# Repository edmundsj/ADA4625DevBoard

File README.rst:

ADA4625 TIA Development Board
===============================
This is a development board for the ADA4625 used as a low-noise a transimpedance amplifier.

Features
----------
- Low noise (140nV/rtHz measured at output with 1MOhm resistor, 140fA/rtHz input-referred)
- M3 standoffs
- Separate SMA inputs for + and -
- Power supplied by banana jacks (V+, V-, GND)
- Optional ESD protection diodes and output load filter
- Test points galore

Issues in Version 1
--------------------
- [FIXED v2.1] Gerbers not updated from v1
- [FIXED v2] No labeling of power, input/outputs
- [FIXED v2] board was unnecessarily large
- [FIXED v2]No name / version number on board

Bill of Materials
-------------------

.. csv-table::
    :header-rows: 1
    :file: bom.csv
    :widths: 25 25 25 25 25

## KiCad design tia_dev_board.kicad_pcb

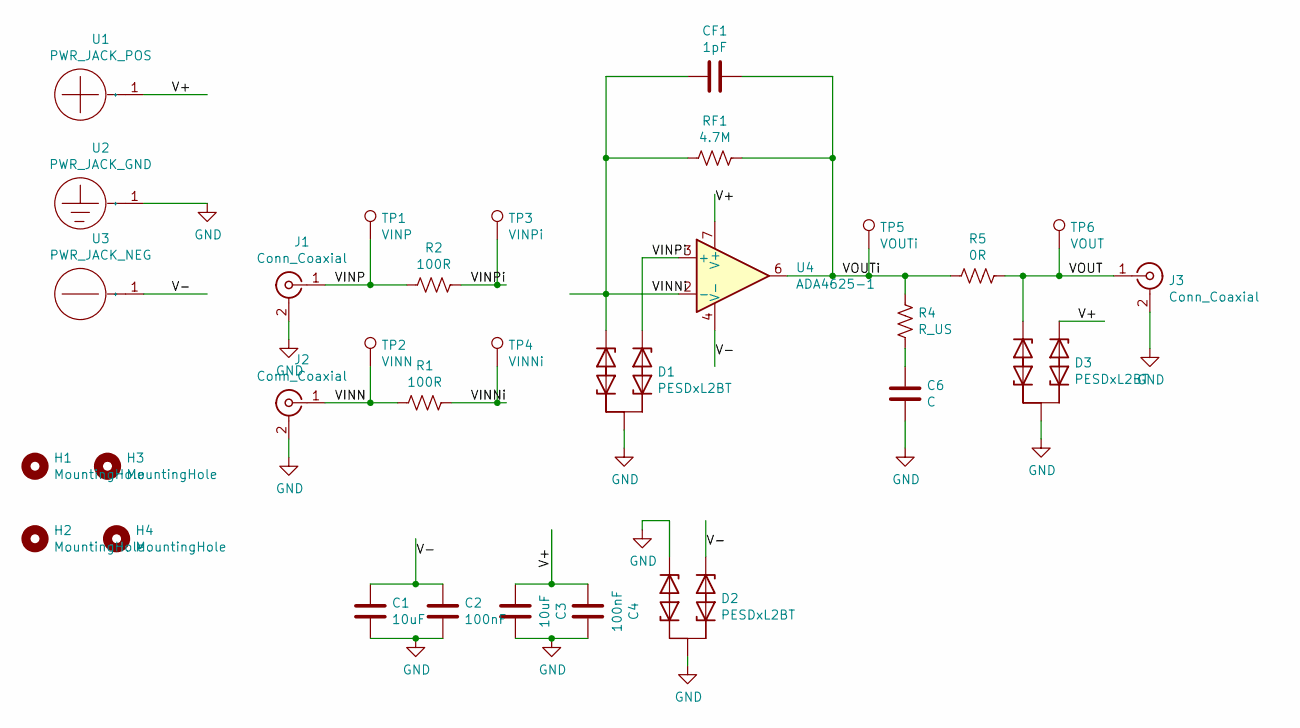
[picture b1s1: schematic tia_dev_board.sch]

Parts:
C1, C3: 10uF; C_0805_2012Metric_Pad1.15x1.40mm_HandSolder
C2, C4: 100nF; C_0805_2012Metric_Pad1.15x1.40mm_HandSolder
C6: C; C_0805_2012Metric_Pad1.15x1.40mm_HandSolder
CF1: 1pF; C_0805_2012Metric_Pad1.15x1.40mm_HandSolder
D1, D2, D3: PESDxL2BT; SC-59_Handsoldering
H1, H2, H3, H4: MountingHole; m3_mounting_hole
J1, J2, J3: Conn_Coaxial; CON-SMA-EDGE-S
R1, R2: 100R; C_0805_2012Metric_Pad1.15x1.40mm_HandSolder
R4: R_US; C_0805_2012Metric_Pad1.15x1.40mm_HandSolder
R5: 0R; C_0805_2012Metric_Pad1.15x1.40mm_HandSolder
RF1: 4.7M; C_0805_2012Metric_Pad1.15x1.40mm_HandSolder
TP1: VINP; TestPoint_Keystone_5000-5004_Miniature
TP2: VINN; TestPoint_Keystone_5000-5004_Miniature
TP3: VINPi; TestPoint_Keystone_5000-5004_Miniature
TP4: VINNi; TestPoint_Keystone_5000-5004_Miniature
TP5: VOUTi; TestPoint_Keystone_5000-5004_Miniature
TP6: VOUT; TestPoint_Keystone_5000-5004_Miniature
U1: PWR_JACK_POS; Banana_Jack_1Pin
U2: PWR_JACK_GND; Banana_Jack_1Pin
U3: PWR_JACK_NEG; Banana_Jack_1Pin
U4: ADA4625-1; SOIC-8-1EP_3.9x4.9mm_P1.27mm_EP2.29x3mm_ThermalVias

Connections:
/V+: C3.2, C4.2, D3.2 (V2), U1.1, U4.7 (V+)
/V-: C1.1, C2.1, D2.2 (V2), U3.1, U4.4 (V-)
/VINN: J2.1 (In), R1.2, TP2.1
/VINNi: CF1.2, D1.1 (V1), R1.1, RF1.2, TP4.1, U4.2 (-)
/VINP: J1.1 (In), R2.2, TP1.1
/VINPi: D1.2 (V2), R2.1, TP3.1, U4.3 (+)
/VOUT: D3.1 (V1), J3.1 (In), R5.1, TP6.1
/VOUTi: CF1.1, R4.1, R5.2, RF1.1, TP5.1, U4.6
GND: C1.2, C2.2, C3.1, C4.1, C6.2, D1.3 (GND), D2.1 (V1), D2.3 (GND), D3.3 (GND), J1.2 (Ext), J2.2 (Ext), J3.2 (Ext), U2.1
unnamed: C6.1, R4.2

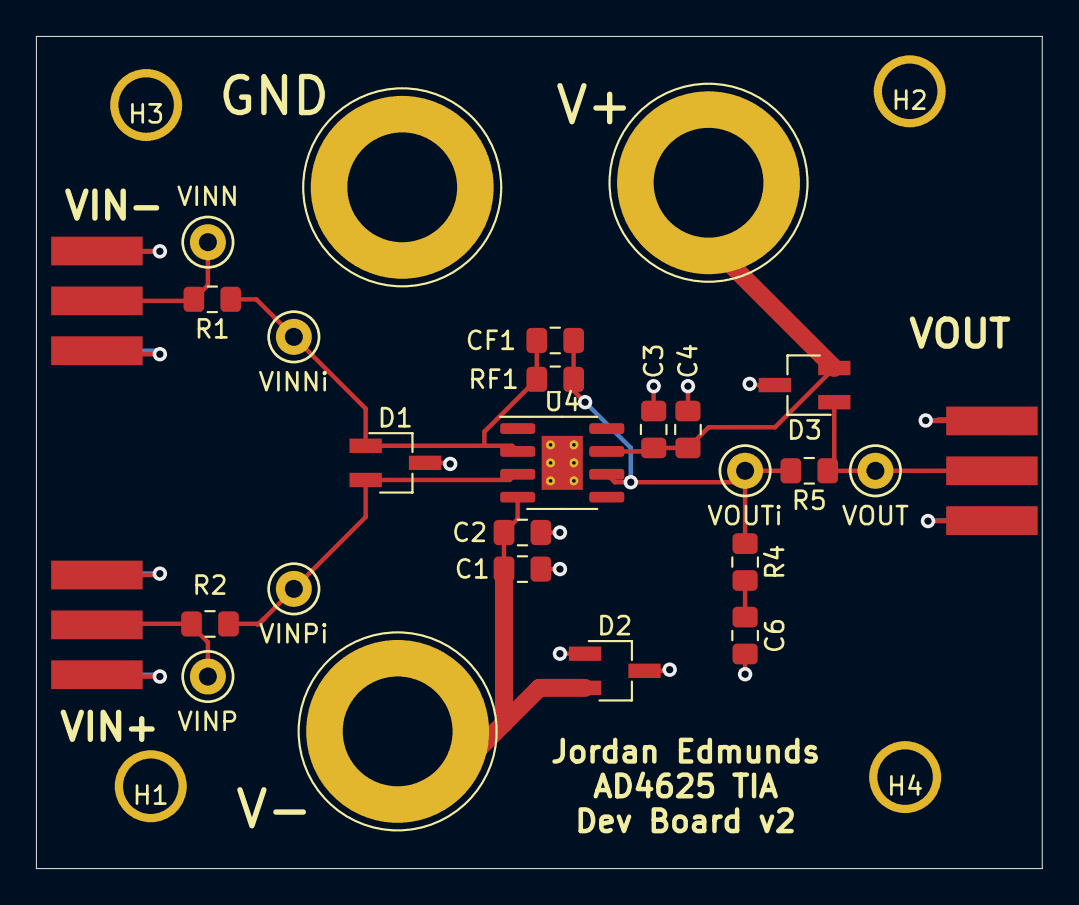
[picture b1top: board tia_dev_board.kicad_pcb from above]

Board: 2 copper layers, 55.9 x 46.2 mm, 31 parts (0 on the bottom side), 10 nets.

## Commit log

2020-10-10 first version of TIA dev board created
2020-10-21 revised PCB according to issues found in version 1
2020-10-22 updated gerbers to correct versions, added README
2020-12-13 added dev board picture
